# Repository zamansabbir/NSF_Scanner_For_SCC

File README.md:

#Firmware details presented in flow-chart

#Details of hand-shaking protocol implemented for the project: 

.

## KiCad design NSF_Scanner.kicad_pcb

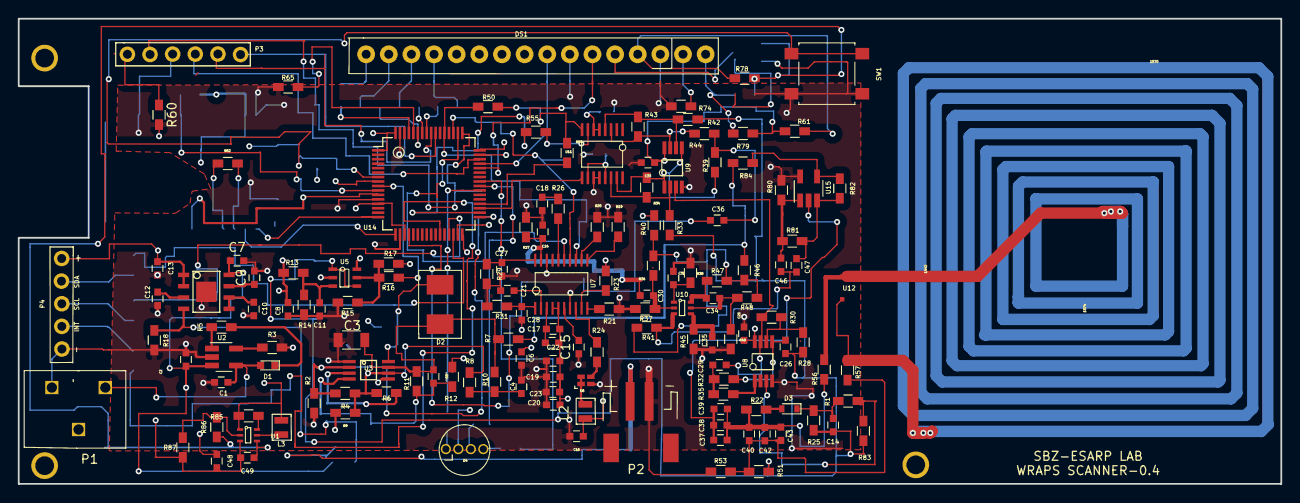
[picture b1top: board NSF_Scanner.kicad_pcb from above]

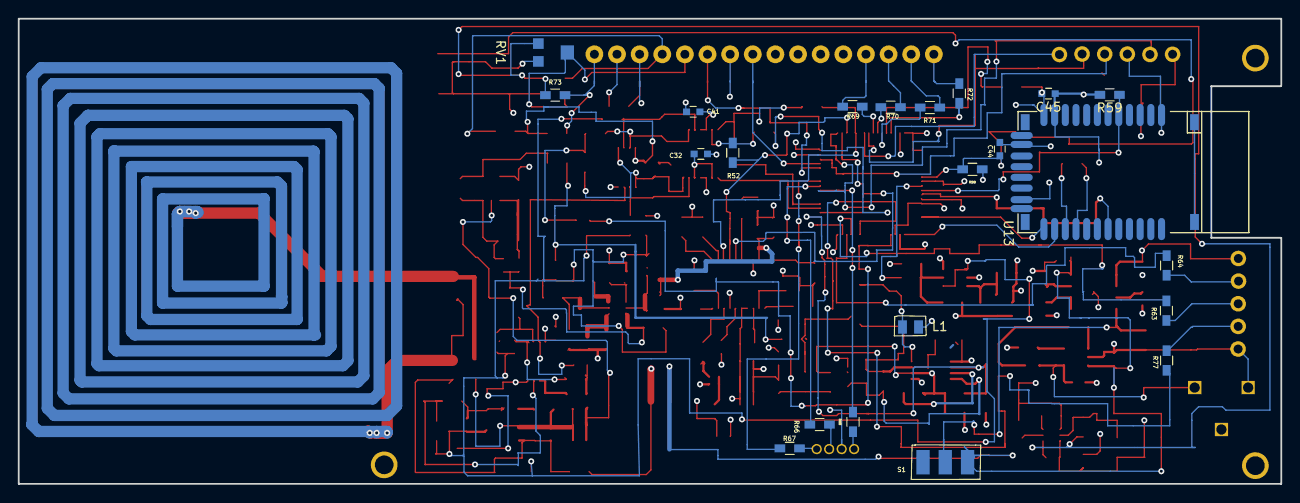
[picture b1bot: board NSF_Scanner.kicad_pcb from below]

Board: 4 copper layers, 141.7 x 52.2 mm, 164 parts (22 on the bottom side), 118 nets.

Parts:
C1, C2: 4.7uF; C_0603
C3: 68uF; C_1206
C4, C11, C15, C16, C19, C20, C21, C24, C25, C27, C28, C32, C33: 100nF; C_0603
C5: 39pF; C_0603
C6: 22uF; C_0603
C7: DNP/10uF; C_0603
C8, C13, C41, C45, C48, C49: 10uF; C_0603
C9, C10, C12, C44: 1uF; C_0603
C14: 510pF; C_0603
C17, C26, C29: 10nF; C_0603
C18: DNP/TBD; C_0603
C22, C23: 2.2uF; C_0603
C30, C34: 1nF; C_0603
C31, C35: 6.8nF; C_0603
C36: 20uF; C_0603
C37, C39: C; C_0603
C38: 10pF; C_0603
C40, C43: TBD/DNP; C_0603
C42: 122pF; C_0603
C46, C47: 68nF; C_0603
D1: LED; LED_0603
D2: D; schottky_power_rectifier
D3: D; D_0603
D4: LED_RCGB; rgb_LED_V3
DS1: LCD-016N002L; LCD_16X2_V2
L1: 6.8uH; L_0805_V2
L2: 0/4.7uH; 4.7uH_v2
L3: 4.7uH; 4.7uH_v2
P1: CONN_01X02; power_jack
P2: CONN_01X02; bat_con_v2
P3: CONN_01X06; ST_Link_Programmer
P4: CONN_01X05; SPO2_v2
R1: 270K; R_0603_HandSoldering
R2, R13, R14, R18, R19, R20, R21, R23, R28, R30, R32, R33, R35, R42, R59: 10K; R_0603_HandSoldering
R3: 2K; R_0603_HandSoldering
R4, R7, R8, R9, R15, R16, R17, R26, R39, R40, R46, R50, R52, R69, R70, R71, R85, R86: 0/DNP; R_0603_HandSoldering
R5, R66, R67, R68: 470; R_0603_HandSoldering
R6: 200K; R_0603_HandSoldering
R10: 500; R_0603_HandSoldering
R11: 150K; R_0603_HandSoldering
R12: 12.4K; R_0603_HandSoldering
R22, R80, R82: 100K; R_0603_HandSoldering
R24, R44, R51, R53, R63, R64, R77, R84: 0; R_0603_HandSoldering
R25: 1M; R_0603_HandSoldering
R27, R29: 200; R_0603_HandSoldering
R31: 6.8K; R_0603_HandSoldering
R34, R43: DNP; R_0603_HandSoldering
R36, R37, R48, R49: 120K; R_0603_HandSoldering
R38, R45: 330; R_0603_HandSoldering
R41, R47: 680; R_0603_HandSoldering
R54, R55, R56, R57, R60, R61, R65, R72, R78, R79: R; R_0603_HandSoldering
R58: 20K; R_0603_HandSoldering
R62: DNP/0; R_0603_HandSoldering
R73, R74: 0/dnp; R_0603_HandSoldering
R81: 22K; R_0603_HandSoldering
R83: 180K; R_0603_HandSoldering
R87: TBD/DNP; R_0603_HandSoldering
RV1: POT; TC_33_pot
S1: SlideSwitch; SLIDE_SWITCH_V2
SW1: SW_DIP_x01; SPST_v2
U1: TPS61220; TPS61222DCKR
U2: MCP73831_SOT; SOT-23-5_HandSoldering
U3: LM2621_v2
U4: ADP7156; ADP7156_v2
U5: LMV791; LMV791_v2
U6: ASCO-50.000MHZ-EK-T3; 50MHZ_OSCI
U7: AD9834; AD9834_v2
U8, U9: MCP6002_v2; mcp6002_s
U10: BJT_DUAL_v2; BJT_DUAL_V3
U11: AD5262; AD5262_v2
U12: PrimaryCoil; d13_v2
U13: RN42; RN42_v2
U14: STM32L476RGT6; STM32L476_LQFP64
U15: dualbjt_emitter; SOT-23-5_HandSoldering

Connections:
5V: C49.1, R73.1, R78.2, R86.1, RV1.1, U1.4
14V: R7.1, R46.1, R84.1
/AnalogFrontEnd/ANT_RX: C37.1, C38.1, C39.1, C40.1, C42.1, C43.1, R22.1, R56.2
/AnalogFrontEnd/ANT_TX: C37.2, C38.2, C39.2, U15.2
/DigitalFronEnd/BT_CON: U13.19, U14.11
/DigitalFronEnd/BT_RX: U13.13, U14.16
/DigitalFronEnd/BT_TX: U13.14, U14.17
/DigitalFronEnd/Contrast: DS1.3, RV1.2
/DigitalFronEnd/D4: R69.2, U14.57
/DigitalFronEnd/D5: R70.2, U14.58
/DigitalFronEnd/D6: R71.2, U14.59
/DigitalFronEnd/D7: R72.2, U14.61
/DigitalFronEnd/INT: R77.1, U14.27
/DigitalFronEnd/NRST: C44.1, R58.2, SW1.1, U14.7
/DigitalFronEnd/i2c2_scl: R63.1, U14.29
/DigitalFronEnd/i2c2_sda: R64.1, U14.30
/DigitalFronEnd/~BT_RESET: R59.1, U13.5, U14.10
/PowerBlock/VBAT: C2.1, C7.1, P2.2, S1.2, U2.3, U4.8
ADC: C36.1, U14.20
BoosterEN: R2.1, R4.2, U3.2, U14.33
DDS_MOSI: R50.1, U7.13, U14.53
DDS_SCLK: R52.1, U7.14, U14.51
DDS_~CS: U7.15, U14.50
E: DS1.6, U14.45
EnableVGnd: R16.2, U14.9
GND: C1.2, C2.2, C3.2, C4.2, C6.2, C7.2, C8.2, C9.2, C10.2, C11.2, C12.2, C13.2, C15.1, C16.2, C18.2, C19.1, C20.2, C21.1, C22.1, C23.2, C24.2, C25.2, C27.2, C28.1, C31.2, C32.2, C33.2, C35.2, C41.2, C44.2, C45.2, C48.2, C49.2, D4.2, DS1.1, DS1.5, P1.2, P2.1, P3.3, P4.5, R2.2, R3.2, R12.2, R14.1, R15.1, R18.2, R19.2, R20.2, R21.2, R23.2, R27.2, R29.2, R31.2, R37.2, R38.2, R45.2, R49.2, R53.1, R60.2, R65.1, R74.1, R80.2, R87.1, RV1.3, SW1.2, U1.3, U2.2, U3.1, U3.5, U4.9, U5.2, U6.2, U7.7, U7.18, U8.4, U9.4, U11.11, U11.12, U13.1, U13.12, U13.28, U13.29, U14.12, U14.18, U14.31, U14.47, U14.63, U15.5
JTCK/SWCLK: P3.2, U14.49
JTDIO/SWO: P3.6, U14.55
JTMS/SWDIO: P3.4, U14.46
NJRST: P3.5, U14.56
unnamed: C1.1, D1.2, P1.1, U2.4
unnamed: C3.1, C5.1, D2.1, R7.2, R10.1, R11.1, U3.7
unnamed: C4.1, R8.1, R10.2
unnamed: C5.2, R11.2, R12.1, U3.4
unnamed: C9.1, U4.7
unnamed: C10.1, U4.5, U4.6
unnamed: C11.1, R13.1, R14.2, U5.3
unnamed: C12.1, U4.3
unnamed: C14.1, D3.1, R1.1, R25.1
unnamed: C15.2, U7.6
unnamed: C17.2, U7.3
unnamed: C21.2, U7.2
unnamed: C24.1, C30.2, R27.1, U7.19
unnamed: C26.1, R32.2, U8.5
unnamed: C27.1, R29.1, U7.20
unnamed: C28.2, R31.1, U7.1
unnamed: C29.1, R32.1, R35.2
unnamed: C29.2, R30.1, U8.7, U9.3
unnamed: C30.1, R36.2, R37.1, U10.2
unnamed: C31.1, R38.1, U10.1
unnamed: C34.1, R47.2, U10.6
unnamed: C34.2, R48.2, R49.1, U10.5
unnamed: C35.1, R45.1, U10.4
unnamed: C36.2, R39.2, R44.2
unnamed: C40.2, C42.2, C43.2, R51.1, R53.2, R57.2
unnamed: C46.1, R80.1, R81.2, U15.1
unnamed: C46.2, C47.2, R41.2, U10.3
unnamed: C47.1, R81.1, R82.2, U15.3
unnamed: D1.1, R5.2
unnamed: D2.2, L1.1, U3.8
unnamed: D3.2, R22.2
unnamed: D4.1, R68.1
unnamed: D4.3, R66.1
unnamed: D4.4, R67.1
unnamed: DS1.2, R61.1, R78.1
unnamed: DS1.11, R69.1
unnamed: DS1.12, R70.1
unnamed: DS1.13, R71.1
unnamed: DS1.14, R72.1
unnamed: DS1.15, R73.2, R79.2
unnamed: DS1.16, R74.2
unnamed: L2.1, U6.1, U6.4
unnamed: L3.2, U1.5
unnamed: P3.1, R60.1
unnamed: P4.2, R64.2
unnamed: P4.3, R63.2
unnamed: P4.4, R77.2
unnamed: R1.2, R83.1, U8.3
unnamed: R3.1, U2.5
unnamed: R4.1, R6.1, R8.2, R9.1, U3.6
unnamed: R5.1, U2.1
unnamed: R6.2, U3.3
unnamed: R15.2, R16.1, R17.1, U5.5
unnamed: R18.1, S1.1, U4.4
unnamed: R19.1, U7.11
unnamed: R20.1, U7.12
unnamed: R21.1, U7.10
unnamed: R23.1, U7.9
unnamed: R24.1, U7.8
unnamed: R24.2, U6.3
unnamed: R26.1, U7.16
unnamed: R28.1, R30.2, U8.6
unnamed: R33.2, R34.1, U9.2, U11.14
unnamed: R34.2, R39.1, U9.1, U9.5, U11.15
unnamed: R35.1, U8.1, U8.2
unnamed: R36.1, R40.2, R41.1, R46.2, R47.1, R48.1
unnamed: R42.2, R43.2, U9.6, U11.4
unnamed: R43.1, R44.1, U9.7, U11.3
unnamed: R50.2, R54.2, U11.8
unnamed: R52.2, R55.2, U11.7
unnamed: R56.1, U12.1
unnamed: R57.1, U12.2
unnamed: R62.1, U13.15
unnamed: R62.2, U13.16
unnamed: R65.2, U14.60
unnamed: R66.2, U14.40
unnamed: R67.2, U14.41
unnamed: R68.2, U14.39
unnamed: R82.1, R84.2, U15.4
unnamed: R85.1, U1.6
unnamed: R86.2, R87.2, U1.2
RS: DS1.4, U14.44
SquareWave: C18.1, R26.2
VCC/2: C14.2, C26.2, R25.2, R28.2, R33.1, R42.1, R51.2, R83.2, U5.1, U5.4
VDD: C6.1, C8.1, C13.1, C16.1, C17.1, C19.2, C20.1, C22.2, C23.1, C25.1, C32.1, C33.1, C41.1, C45.1, C48.1, L1.2, L2.2, L3.1, P4.1, R9.2, R13.2, R17.2, R40.1, R58.1, R59.2, R61.2, R79.1, R85.2, U1.1, U4.1, U4.2, U5.6, U7.4, U7.5, U8.8, U9.8, U11.5, U11.6, U11.10, U11.13, U13.11, U14.1, U14.13, U14.19, U14.32, U14.48, U14.64
VGA_CLK: R55.1, U14.34
VGA_SDI: R54.1, U14.36
VGA_~CS: U11.9, U14.35

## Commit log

2019-09-05 Firmware
    Firmware is developed for STM32 micrcontroller in Keil developer
2019-09-05 Create Firmware
2020-09-30 Create README.rd
    Picture added for project description
2020-09-30 Rename README.rd to README.md
